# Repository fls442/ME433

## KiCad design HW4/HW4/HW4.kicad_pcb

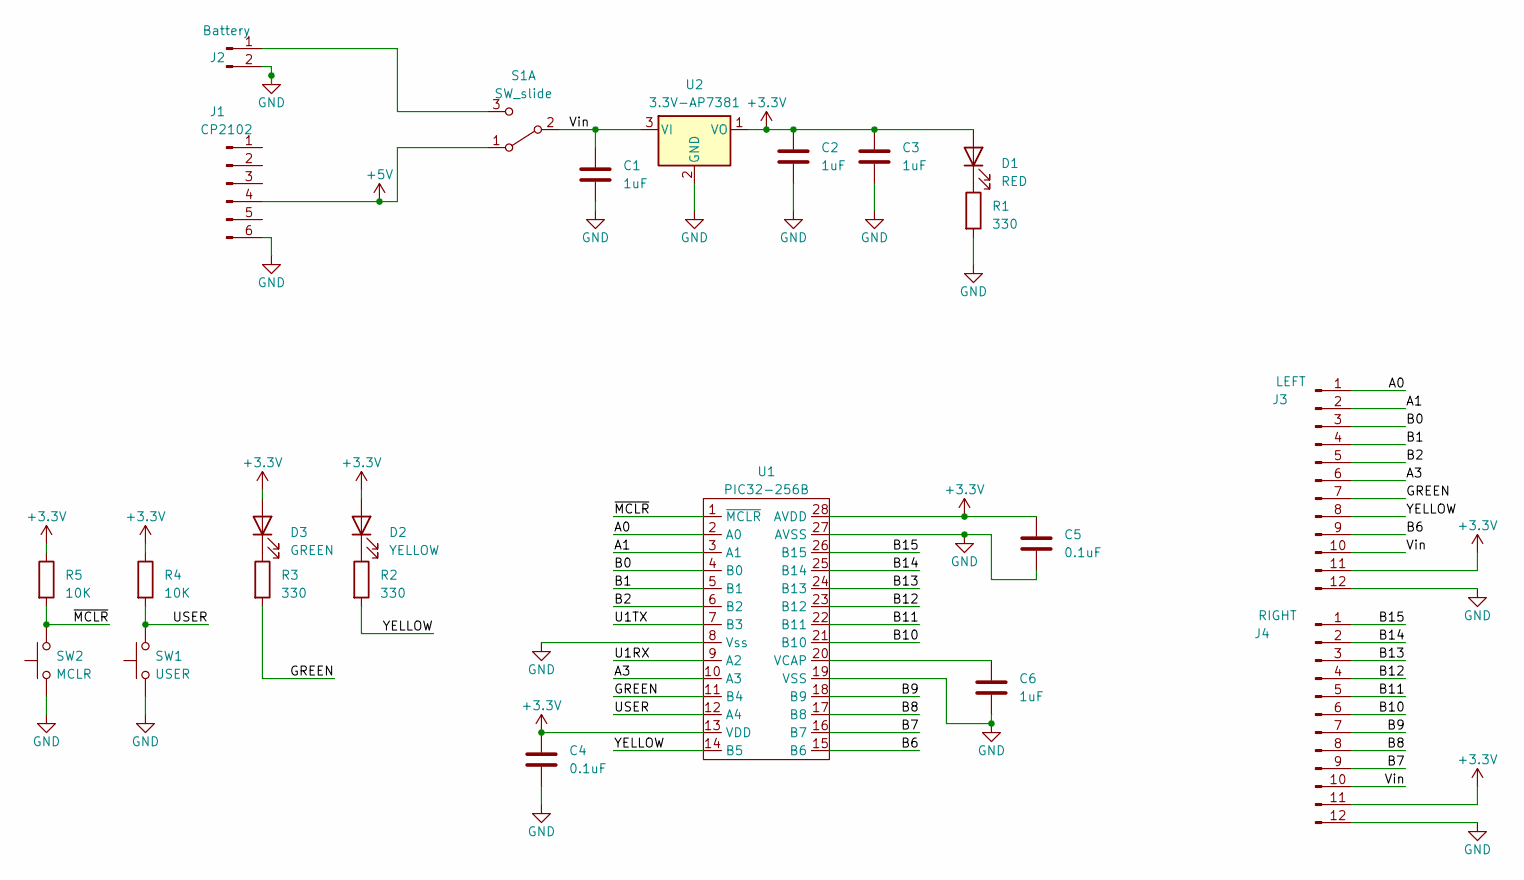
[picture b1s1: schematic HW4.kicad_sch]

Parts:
C1, C2, C3, C6: 1uF; C_Disc_D5.1mm_W3.2mm_P5.00mm
C4, C5: 0.1uF; C_Disc_D3.4mm_W2.1mm_P2.50mm
D1: RED; LED_D3.0mm
D2: YELLOW; LED_D3.0mm
D3: GREEN; LED_D3.0mm
J1: CP2102; PinSocket_1x06_P2.54mm_Vertical
J2: Battery; PinSocket_1x02_P2.54mm_Vertical
J3: LEFT; PinSocket_1x12_P2.54mm_Vertical
J4: RIGHT; PinSocket_1x12_P2.54mm_Vertical
R1, R2, R3: 330; R_Axial_DIN0207_L6.3mm_D2.5mm_P7.62mm_Horizontal
R4, R5: 10K; R_Axial_DIN0207_L6.3mm_D2.5mm_P7.62mm_Horizontal
S1: SW_slide; PinSocket_1x03_P2.54mm_Vertical
SW1: USER; PinSocket_1x03_P2.54mm_Vertical
SW2: MCLR; PinSocket_1x03_P2.54mm_Vertical
U1: PIC32-256B; DIP-28_W7.62mm_Socket
U2: 3.3V-AP7381; TO-92L_Inline

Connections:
+3.3V: C2.1, C3.1, C4.1, C5.1, D1.2 (A), D2.2 (A), D3.2 (A), J3.11, J4.11, R4.1, R5.1, U1.13 (VDD), U1.28 (AVDD), U2.1 (VO)
+5V: J1.4, S1.1 (A)
/A0: J3.1, U1.2 (A0)
/A1: J3.2, U1.3 (A1)
/A3: J3.6, U1.10 (A3)
/B0: J3.3, U1.4 (B0)
/B1: J3.4, U1.5 (B1)
/B2: J3.5, U1.6 (B2)
/B6: J3.9, U1.15 (B6)
/B7: J4.9, U1.16 (B7)
/B8: J4.8, U1.17 (B8)
/B9: J4.7, U1.18 (B9)
/B10: J4.6, U1.21 (B10)
/B11: J4.5, U1.22 (B11)
/B12: J4.4, U1.23 (B12)
/B13: J4.3, U1.24 (B13)
/B14: J4.2, U1.25 (B14)
/B15: J4.1, U1.26 (B15)
/GREEN: J3.7, R3.2, U1.11 (B4)
/U1RX: U1.9 (A2)
/U1TX: U1.7 (B3)
/USER: R4.2, SW1.2, U1.12 (A4)
/Vin: C1.1, J3.10, J4.10, S1.2 (B), U2.3 (VI)
/YELLOW: J3.8, R2.2, U1.14 (B5)
/~MCLR: R5.2, SW2.2, U1.1 (~MCLR)
GND: C1.2, C2.2, C3.2, C4.2, C5.2, C6.2, J1.6, J2.2, J3.12, J4.12, R1.2, SW1.1, SW2.1, U1.8 (Vss), U1.19 (VSS), U1.27 (AVSS), U2.2 (GND)
unnamed: D1.1 (K), R1.1
unnamed: D2.1 (K), R2.1
unnamed: D3.1 (K), R3.1
unnamed: J2.1, S1.3 (C)
unnamed: C6.1, U1.20 (VCAP)

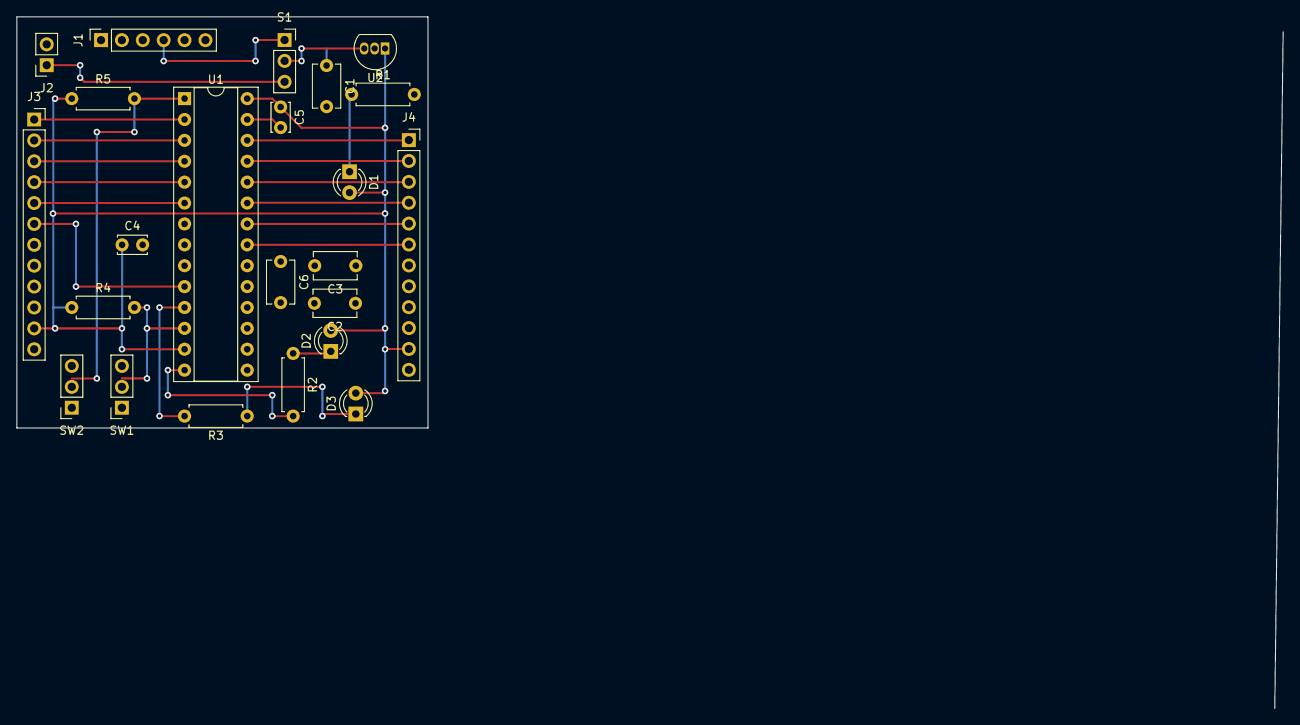
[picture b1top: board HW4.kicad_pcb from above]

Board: 2 copper layers, 154.0 x 84.1 mm, 23 parts (0 on the bottom side), 29 nets.

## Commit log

2023-04-18 HW2 Push
2023-04-24 idk what happened lol
2023-04-25 HW3 Update
2023-05-07 hw5 (in progress)
    idk why but the PIC refuses to exit bootloader mode when I try to upload the code
2023-05-08 HW5 DONE
    LFG BABIEEEEE
2023-05-28 HW6 almost working
2023-05-28 HW6 Working :D
2023-05-30 HW7 Done
2023-05-30 HW 8
2023-05-31 HW9 Done-zo
2023-05-31 forgot my graph titles so i added txt file
2023-06-04 HW10 DONE
2023-06-08 HW4 Done lawl
2023-06-08 HW done for real w/ images
2023-06-08 HW11 Done
2023-06-08 HW14 DONEEE!!!!!!!!!!
